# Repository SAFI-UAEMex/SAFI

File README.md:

<p align="center">
  <table border="0" cellpadding="0" cellspacing="0">
    <tr>
      <td align="center" valign="middle">
        
      </td>
      <td width="20"></td> <td align="center" valign="middle">
        
      </td>
    </tr>
  </table>
</p>

# 🚀 Proyecto Aeroespacial SAFI (Sistema Autónomo de Vuelo Integrado)

Bienvenido al repositorio maestro del **Capítulo Estudiantil SAFI - UAEMex**. 

Este espacio centraliza el trabajo de ingeniería multidisciplinario de todas las divisiones de nuestro equipo. Nuestro objetivo es documentar, versionar y unificar el ciclo de vida completo de nuestros vehículos aeroespaciales: desde los cálculos conceptuales y simulaciones aerodinámicas, hasta el diseño electrónico, la programación de la computadora de vuelo y la manufactura de las aeroestructuras.

---

## 🎯 Propósito del Repositorio

Para asegurar el control de calidad, la trazabilidad de los errores y la colaboración fluida entre los distintos departamentos de ingeniería, este monorepositorio integra:
* **Códigos y Firmware:** Software de vuelo, algoritmos de telemetría y sistemas de ignición.
* **Memorias de Cálculo:** Justificaciones matemáticas, simulaciones de trayectoria y análisis de esfuerzos estructurales.
* **Diseño CAD/EDA:** Archivos fuente de piezas mecánicas en 3D y diagramas de circuitos impresos (PCBs).
* **Sistemas de Sub-Repositorios:** Módulos independientes de ingeniería vinculados a este núcleo maestro.

---

## ⚙️ Arquitectura del Sistema (Divisiones)

El proyecto está dividido en subsistemas críticos de ingeniería. Cada división mantiene su propia estructura de trabajo y documentación dentro de su directorio:

### 📡 1. Aviónica y Telemetría (`/AVIONICA`)
Desarrollo del "cerebro" del vehículo (Computadora LANIAKEA).
* Diseño electrónico de PCBs (KiCad / Altium).
* Firmware de adquisición de datos (Sensores Inerciales y Atmosféricos).
* Arquitectura de comunicación y protocolos (I2C, SPI, UART).
* *Nota: Esta carpeta opera mediante submódulos de Git (Ver sección "Guía de Clonación").*

### 🛠️ 2. Aeroestructuras (`/AEROESTRUCTURAS`)
Diseño mecánico y análisis de viabilidad del fuselaje y componentes.
* Archivos CAD (SolidWorks, Fusion360 o FreeCAD).
* Simulaciones de Análisis de Elementos Finitos (FEA).
* Planos de manufactura y tolerancia.

### 🔥 3. Propulsión (`/PROPULSION`)
Ingeniería de motores y sistemas de empuje.
* Memorias de cálculo termodinámico y perfiles de empuje.
* Diseño de toberas y carcasas de motor.
* Registros de telemetría de bancos de prueba estáticos.

### 🪂 4. Sistema de Recuperación (`/RECUPERACION`)
Sistemas de despliegue y descenso seguro.
* Cálculos de arrastre (Drag) y dimensionamiento de paracaídas.
* Mecanismos de eyección electromecánica y pirotécnica.
* Lógica de despliegue en el firmware de Aviónica.

---

## 💻 Guía de Clonación (¡Importante!)

Debido a que este proyecto utiliza una arquitectura profesional de **Submódulos de Git** para manejar repositorios independientes (como las librerías de KiCad), un clonado normal no descargará todo el código.

Para obtener el cohete completo con todas sus carpetas, los miembros del equipo deben clonar este repositorio por primera vez usando la bandera `--recurse-submodules`:

```bash
git clone --recurse-submodules [https://github.com/SAFI-UAEMex/SAFI.git](https://github.com/SAFI-UAEMex/SAFI.git)

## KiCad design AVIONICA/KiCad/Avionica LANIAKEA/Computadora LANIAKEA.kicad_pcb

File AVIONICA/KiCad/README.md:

# KiCad
# Diseño Electrónico en KiCad - SAFI

Bienvenido al repositorio oficial de recursos y diseño electrónico del **Capítulo Estudiantil SAFI**. 

Este espacio está dedicado a estandarizar, almacenar y documentar nuestros flujos de trabajo utilizando **KiCad EDA**. Nuestro objetivo principal es facilitar la colaboración entre todos los miembros del equipo, mantener una biblioteca unificada de componentes y optimizar nuestro proceso de fabricación interna de placas de circuito impreso (PCBs).

---

## Propósito del Repositorio

Para asegurar la calidad y compatibilidad en todos los proyectos de ingeniería del capítulo, este repositorio centraliza:
- **Bibliotecas Propias:** Símbolos esquemáticos y huellas (footprints) validados para los componentes que utilizamos frecuentemente.
- **Reglas de Diseño (DRC):** Configuraciones estandarizadas para garantizar que cualquier miembro diseñe placas que nuestra máquina CNC pueda fresar sin problemas.
- **Plantillas Base:** Archivos de KiCad pre-configurados para acelerar el desarrollo de nuevos circuitos.

## Flujo de Manufactura del Capítulo

Fomentamos una cultura de "Hazlo tú mismo" (DIY). Nuestro flujo de trabajo oficial para llevar los diseños de la pantalla a la placa de baquelita es:

1. **[KiCad](https://www.kicad.org/):** Creación del diagrama esquemático, ruteo de la PCB y exportación de archivos Gerber.
2. **[FlatCAM 8.991](https://drive.google.com/file/d/1pwMMPqekb8oLhkwjraOCaSqU5r90mv8D/view?usp=drive_link):** Procesamiento de los Gerbers para generar las trayectorias de la herramienta (G-code) aislando las pistas.
3. **[Candle](https://drive.google.com/drive/folders/1Qzr3Ldz9wdj51mxDhc2Xyh02n26Dh03L?usp=drive_link):** Control de la máquina CNC para el fresado de pistas, perforación de agujeros (drill) y corte del contorno de la placa.

## 📁 Estructura del Repositorio

- 📂 `/Bibliotecas_Capitulo` - Archivos `.kicad_sym` (símbolos), `.kicad_mod` (huellas) y modelos 3D (`.step`).
- 📂 `/Plantillas_KiCad` - Proyectos base con los grosores de pista y separaciones correctas para nuestro router CNC.
- 📂 `/Guias_y_Tutoriales` - Documentación paso a paso para los nuevos miembros.

## Cómo Colaborar (Para Miembros)

Si eres parte del equipo de electrónica y vas a contribuir a este repositorio:
1. Sincroniza siempre tu carpeta local antes de abrir KiCad abriendo tu terminal y ejecutando: `git pull origin main`.
2. Si diseñas un símbolo o footprint nuevo, asegúrate de guardarlo en la carpeta `/Bibliotecas_Capitulo` para que el resto del equipo pueda aprovecharlo.
3. Guarda tus avances constantemente y haz commits descriptivos (ej. `git commit -m "Agregada guía de grosores de pista para FlatCAM"`).
---
*Repositorio mantenido por el área de Electrónica del Capítulo. ¡El limite son las estrellas!*

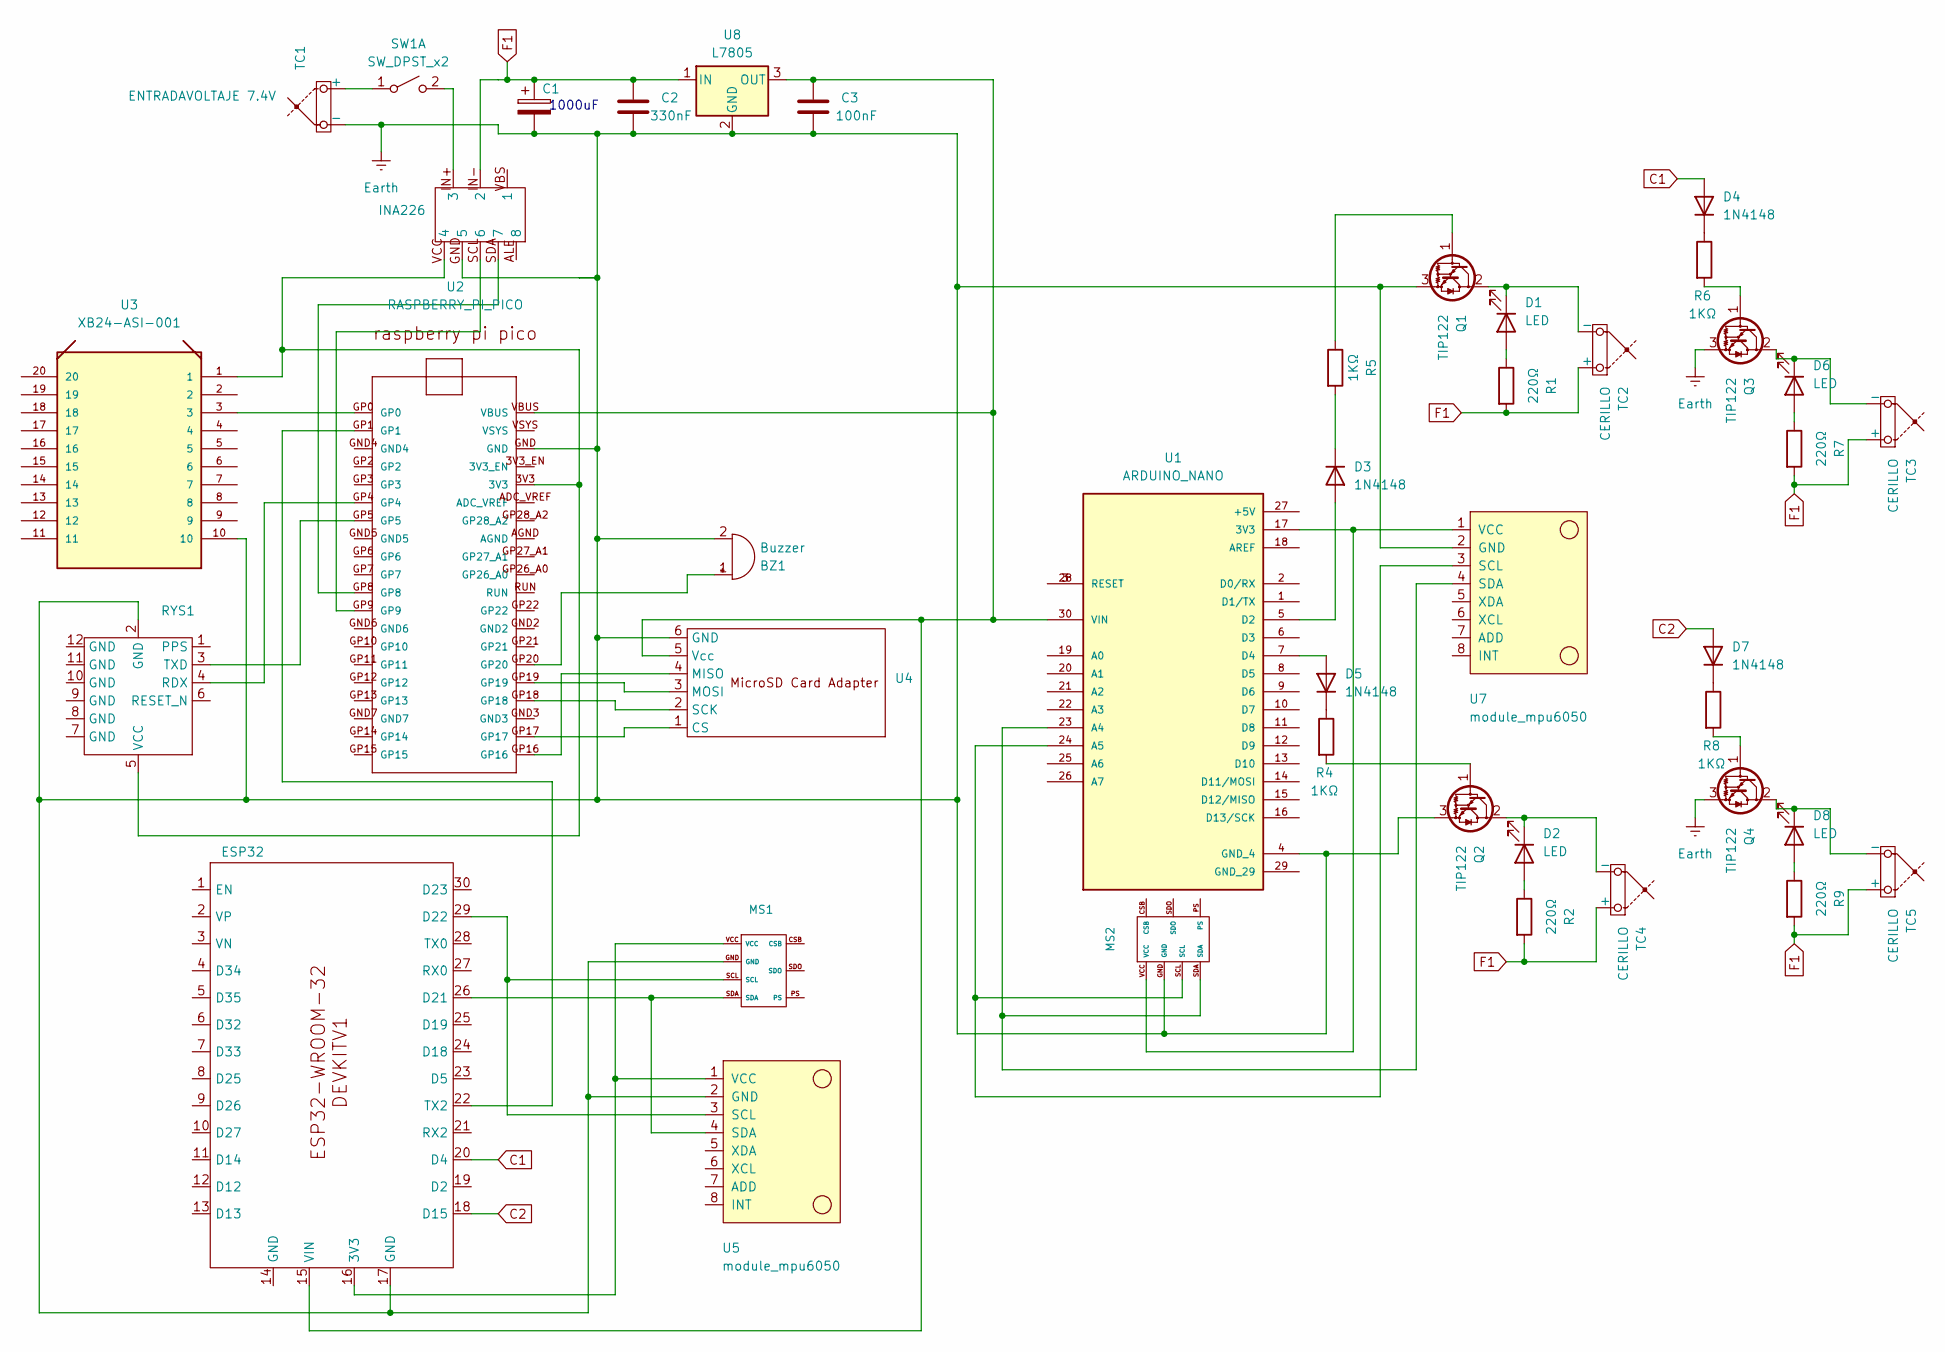
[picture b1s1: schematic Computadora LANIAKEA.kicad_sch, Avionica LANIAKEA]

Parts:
BZ1: Buzzer; Buzzer_12x9.5RM7.6
C1: C_Polarized; CP_Radial_D12.5mm_P5.00mm
C2: 330nF; C_Axial_L3.8mm_D2.6mm_P7.50mm_Horizontal
C3: 100nF; C_Axial_L3.8mm_D2.6mm_P7.50mm_Horizontal
D1, D2, D6, D8: LED; LED_D5.0mm_Clear
D3, D4, D5, D7: 1N4148; D_DO-35_SOD27_P7.62mm_Horizontal
ESP32: ESP32DEVIKITV1
INA226: INA226
MS1, MS2: MS5611
Q1, Q2, Q3, Q4: TIP122; TO-220-3_Vertical
R1, R2, R7, R9: 220Ω; R_Axial_DIN0204_L3.6mm_D1.6mm_P7.62mm_Horizontal
R4, R5, R6, R8: 1KΩ; R_Axial_DIN0204_L3.6mm_D1.6mm_P7.62mm_Horizontal
RYS1: Reyax_RYS352A
SW1: SW_DPST_x2; Untitled
TC1: ENTRADAVOLTAJE 7.4V; TerminalBlock_MaiXu_MX126-5.0-02P_1x02_P5.00mm
TC2, TC3, TC4, TC5: CERILLO; TerminalBlock_MaiXu_MX126-5.0-02P_1x02_P5.00mm
U1: ARDUINO_NANO; MODULE_ARDUINO_NANO; PARTREV 30/06/2021
U2: RASPBERRY_PI_PICO
U3: XB24-ASI-001; DIP-20
U4: Module_MicroSD_Gen
U5, U7: module_mpu6050
U8: L7805; TO-220-3_Vertical

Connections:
C1: D4.2 (A), ESP32.20 (D4)
C2: D7.2 (A), ESP32.18 (D15)
Earth: BZ1.2 (-), C1.2, C2.2, C3.2, ESP32.17 (GND), INA226.GND (5), MS1.GND, MS2.GND, Q1.3 (E), Q2.3 (E), Q3.3 (E), Q4.3 (E), RYS1.2 (GND), TC1.2 (-), U1.4 (GND_4), U2.GND, U3.10, U4.6 (GND), U5.2 (GND), U7.2 (GND), U8.2 (GND)
F1: C1.1, C2.1, INA226.IN- (2), R1.2, R2.2, R7.2, R9.2, TC2.1 (+), TC3.1 (+), TC4.1 (+), TC5.1 (+), U8.1 (IN)
unnamed: BZ1.1 (+), U2.GP20
unnamed: D1.2 (A), R1.1
unnamed: D1.1 (K), Q1.2 (C), TC2.2 (-)
unnamed: D2.2 (A), R2.1
unnamed: D2.1 (K), Q2.2 (C), TC4.2 (-)
unnamed: D3.2 (A), U1.5 (D2)
unnamed: D3.1 (K), R5.2
unnamed: D4.1 (K), R6.1
unnamed: D5.2 (A), U1.7 (D4)
unnamed: D5.1 (K), R4.1
unnamed: D6.2 (A), R7.1
unnamed: D6.1 (K), Q3.2 (C), TC3.2 (-)
unnamed: D7.1 (K), R8.1
unnamed: D8.2 (A), R9.1
unnamed: D8.1 (K), Q4.2 (C), TC5.2 (-)
unnamed: ESP32.16 (3V3), MS1.VCC, U5.1 (VCC)
unnamed: ESP32.26 (D21), MS1.SDA, U5.4 (SDA)
unnamed: ESP32.29 (D22), MS1.SCL, U5.3 (SCL)
unnamed: ESP32.22 (TX2), U2.GP1
unnamed: C3.1, ESP32.15 (VIN), U1.30 (VIN), U2.VBUS, U4.5 (Vcc), U8.3 (OUT)
unnamed: INA226.IN+ (3), SW1.2 (B)
unnamed: INA226.VCC (4), RYS1.5 (VCC), U2.3V3, U3.1
unnamed: INA226.SCL (6), U2.GP9
unnamed: INA226.SDA (7), U2.GP8
unnamed: Q1.1 (B), R5.1
unnamed: Q2.1 (B), R4.2
unnamed: Q3.1 (B), R6.2
unnamed: Q4.1 (B), R8.2
unnamed: RYS1.4 (RDX), U2.GP4
unnamed: RYS1.3 (TXD), U2.GP5
unnamed: SW1.1 (A), TC1.1 (+)
unnamed: MS2.VCC, U1.17 (3V3), U7.1 (VCC)
unnamed: MS2.SDA, U1.23 (A4), U7.4 (SDA)
unnamed: MS2.SCL, U1.24 (A5), U7.3 (SCL)
unnamed: U1.3 (RESET), U1.28 (RESET)
unnamed: U2.GP0, U3.3
unnamed: U2.GP17, U4.1 (CS)
unnamed: U2.GP16, U4.4 (MISO)
unnamed: U2.GP19, U4.3 (MOSI)
unnamed: U2.GP18, U4.2 (SCK)

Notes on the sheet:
1000uF

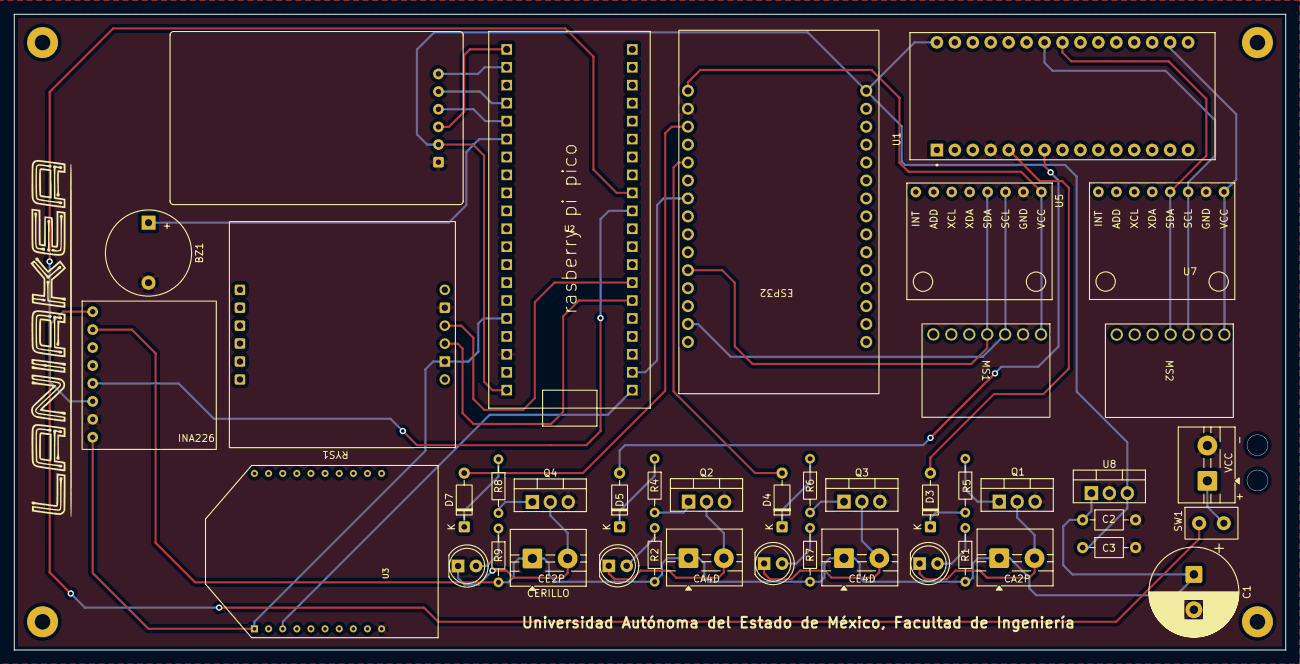
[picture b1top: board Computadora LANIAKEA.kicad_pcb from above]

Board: 2 copper layers, 180.0 x 90.0 mm, 42 parts (0 on the bottom side), 44 nets.

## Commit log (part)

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2026-04-09 Agregando repositorios de KiCad y Altium como submódulos del proyecto SAFI
2026-04-09 move firmwawre
2026-04-09 crear carpeta de imagenes locales
2026-04-09 Carga de Logos
2026-04-13 push documentation
2026-04-13 Add recovery documentation link to README
2026-04-13 Rename RECUPERACIÓN.md to README.md
2026-04-13 Rename XITZIN II.md to README.md
